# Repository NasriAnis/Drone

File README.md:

# ESP32 Mini Drone

A tiny DIY quadcopter built around an ESP32, brushed coreless motors, and a hand-written flight controller.

The project is split in two firmware images, both built with ESP-IDF:

- `firmware/drone`: runs on the drone (IMU, PID stabilisation, motor PWM)
- `firmware/controller`: runs on the handheld remote (joystick via ADC)

> [!WARNING]
> **Testing phase.** This project is under active development. Expect bugs and breaking changes, and **always test with the propellers removed** until you trust the flight controller.

## Repository layout

```
Drone/
├── firmware/
│   ├── components/        # Shared code between drone and controller
│   ├── controller/        # Remote control firmware
│   │   └── main/          # adc, joystick, main
│   ├── drone/             # Drone firmware
│   │   └── main/          # i2c, ledc, motors, mpu, pid, main
│   └── settings.h         # Settings shared by both firmwares
├── schematics/            # Wiring and PCB files
├── LICENSE
└── README.md
```

## Requirements

Software:
- Linux or macOS (Windows works too, but the commands below are for a Unix shell)
- ESP-IDF v5.x

Hardware:
- An ESP32 dev board for the drone and one for the controller
- A USB cable that carries data (not charge-only)
- 4 Motors
- 4 Mosfets
- 4 joysticks
- MPU
- Battery

What i used:
- ESP32 C3 pro mini for the drone
- ESP32 S3 for the controller
- 8520 Motors x4
- 55mm propelers x4
- AO3400 Mosfets x4
- 6500 MPU x1
- Joysticks x2
- Battery

## 1. ESP-IDF framework and env setup

Install ESP-IDF by following the official guide, and select the ESP32 target when it asks for one: https://docs.espressif.com/projects/esp-idf/en/stable/esp32/get-started/index.html#installation

> **Important:** you must load the ESP-IDF environment in every new terminal before using `idf.py`. If you skip this, `idf.py` will not be found.

## 2. Clone the project

```bash
git clone https://github.com/NasriAnis/Drone Drone
cd Drone
```

## 3. Build and flash the drone and controller firmware

Go into the drone project:
```bash
cd firmware/drone
```

Set the chip target. This only needs to be done once per project (it resets `build/` and regenerates the config):
```bash
idf.py set-target <your-dev-board>
```

Build flash and monitor for errors:
```bash
idf.py build flash monitor -p <esp-port>
```

To leave the monitor, press `Ctrl+]` then disconnect the device.

Do the same steps for the `firmware/controller` folder.

## Settings

Shared values (pins, PID gains, limits, communication parameters) live in `firmware/settings.h`. After editing it, rebuild both firmwares and flash them again so they stay in sync.

## Editor / LSP (clangd)

To get proper completion and diagnostics, point clangd at the generated `compile_commands.json`. After a build, link it to the repo root:

```bash
ln -sf firmware/drone/build/compile_commands.json compile_commands.json
```

## License

See [LICENSE](LICENSE).

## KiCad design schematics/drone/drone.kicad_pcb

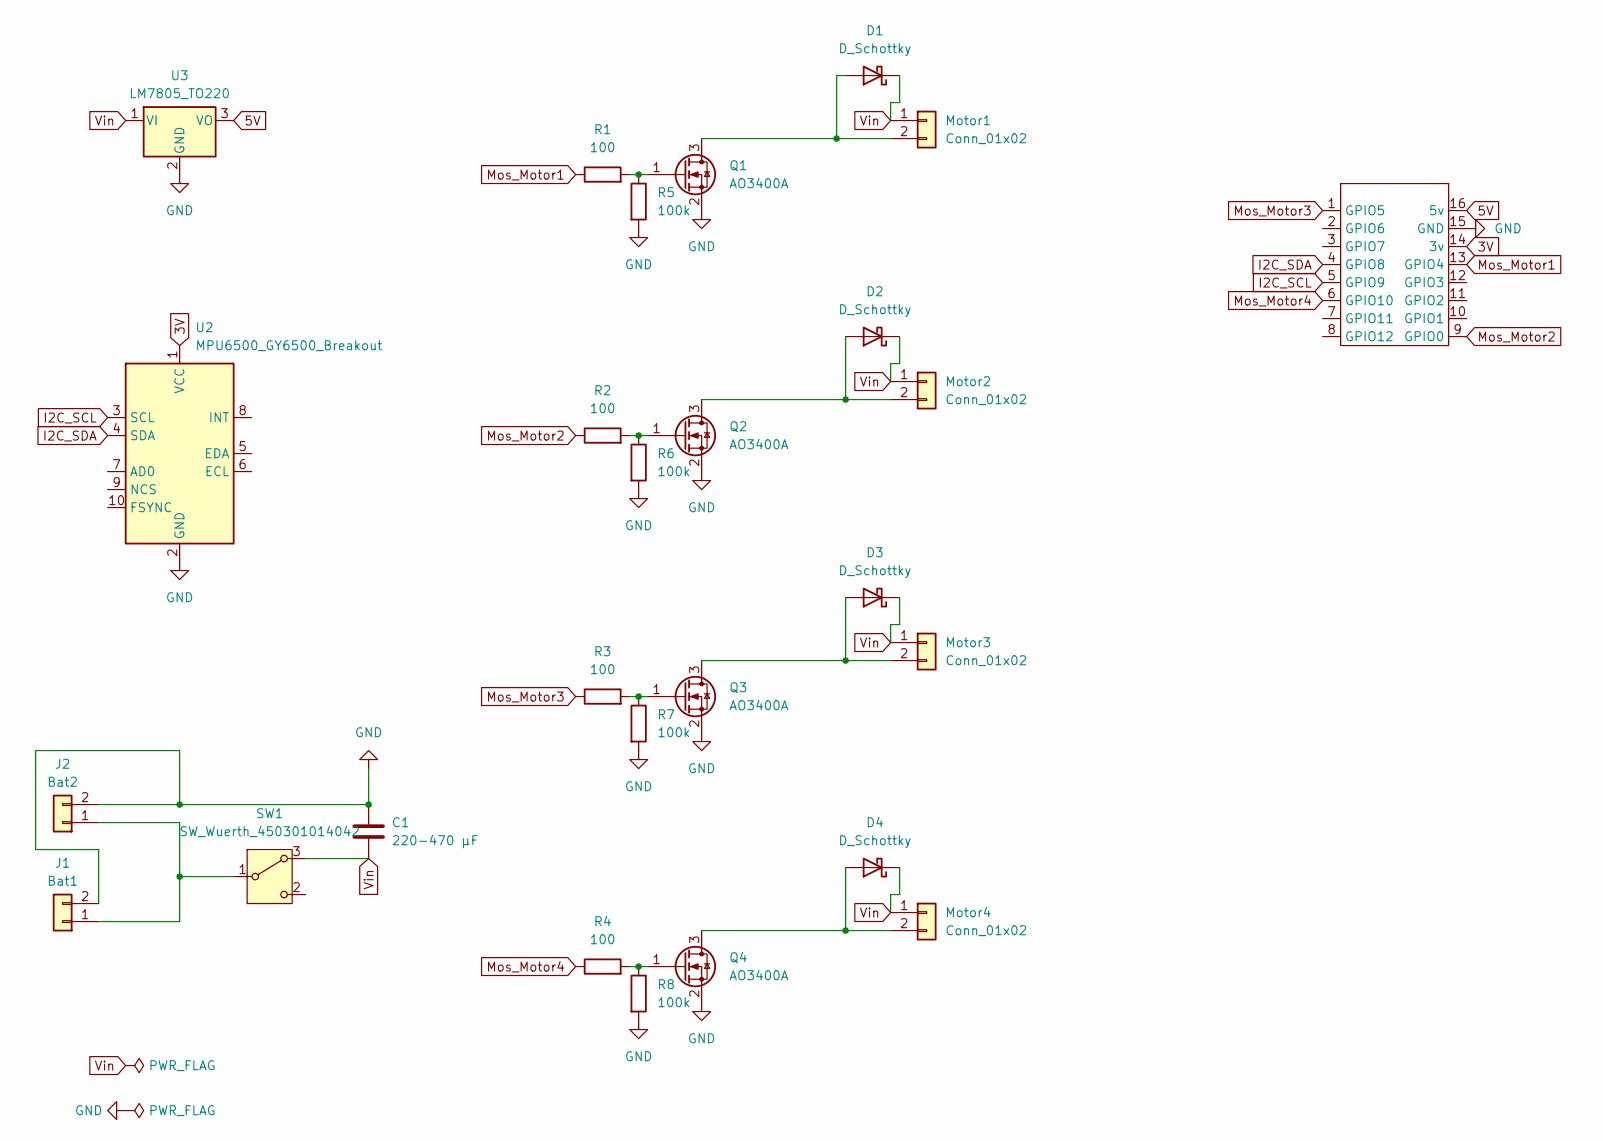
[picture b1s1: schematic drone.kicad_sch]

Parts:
C1: 220-470 µF; CP_Radial_D6.3mm_P2.50mm
D1, D2, D3, D4: D_Schottky; D_DO-35_SOD27_P7.62mm_Horizontal
J1: Bat1; PinHeader_1x02_P2.54mm_Vertical
J2: Bat2; PinHeader_1x02_P2.54mm_Vertical
Motor1, Motor2, Motor3, Motor4: Conn_01x02; PinHeader_1x02_P2.54mm_Vertical
Q1, Q2, Q3, Q4: AO3400A; SOT-23
R1, R2, R3, R4: 100; R_Axial_DIN0207_L6.3mm_D2.5mm_P10.16mm_Horizontal
R5, R6, R7, R8: 100k; R_Axial_DIN0207_L6.3mm_D2.5mm_P10.16mm_Horizontal
SW1: SW_Wuerth_450301014042; SW_Slide-03_Wuerth-WS-SLTV_10x2.5x6.4_P2.54mm
U2: MPU6500_GY6500_Breakout; PinHeader_1x10_P2.54mm_Vertical
U3: LM7805_TO220; SOT-223-3_TabPin2
U4: ESP32-C3-Pro-Mini

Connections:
3V: U2.1 (VCC), U4.14 (3v)
5V: U3.3 (VO), U4.16 (5v)
GND: C1.2, J1.2, J2.2, Q1.2 (S), Q2.2 (S), Q3.2 (S), Q4.2 (S), R5.2, R6.2, R7.2, R8.2, U2.2 (GND), U3.2 (GND), U4.15 (GND)
I2C_SCL: U2.3 (SCL), U4.5 (GPIO9)
I2C_SDA: U2.4 (SDA), U4.4 (GPIO8)
Mos_Motor1: R1.1, U4.13 (GPIO4)
Mos_Motor2: R2.1, U4.9 (GPIO0)
Mos_Motor3: R3.1, U4.1 (GPIO5)
Mos_Motor4: R4.1, U4.6 (GPIO10)
unnamed: D1.2 (A), Motor1.2, Q1.3 (D)
unnamed: D2.2 (A), Motor2.2, Q2.3 (D)
unnamed: D3.2 (A), Motor3.2, Q3.3 (D)
unnamed: D4.2 (A), Motor4.2, Q4.3 (D)
unnamed: J1.1, J2.1, SW1.1 (B)
unnamed: Q1.1 (G), R1.2, R5.1
unnamed: Q2.1 (G), R2.2, R6.1
unnamed: Q3.1 (G), R3.2, R7.1
unnamed: Q4.1 (G), R4.2, R8.1
Vin: C1.1, D1.1 (K), D2.1 (K), D3.1 (K), D4.1 (K), Motor1.1, Motor2.1, Motor3.1, Motor4.1, SW1.3 (A), U3.1 (VI)

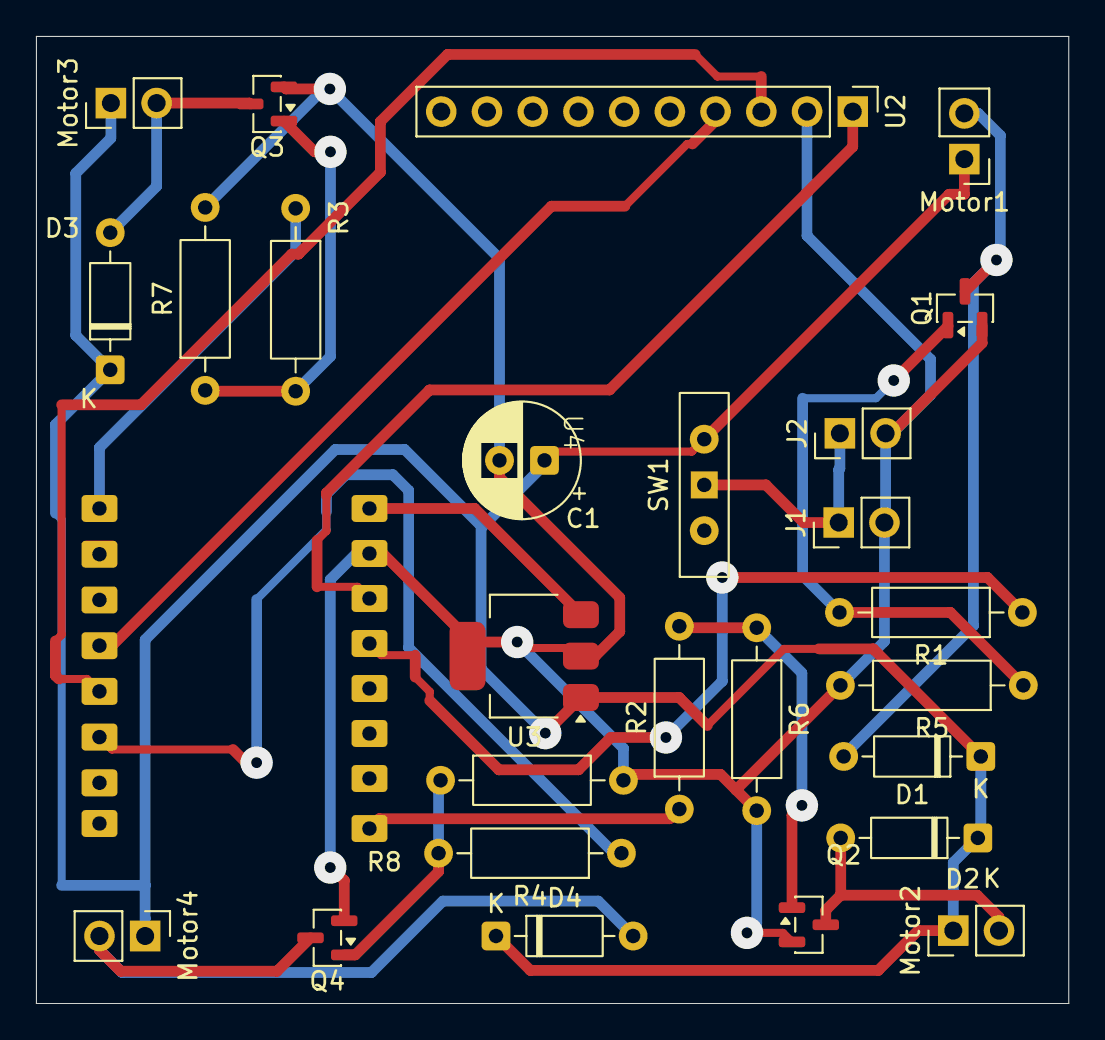
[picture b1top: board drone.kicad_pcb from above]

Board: 2 copper layers, 57.3 x 53.7 mm, 27 parts (0 on the bottom side), 19 nets.
